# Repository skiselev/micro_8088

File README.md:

# Micro 8088
IBM XT Compatible Processor Board based on Faraday FE2010/FE2010A chipset

## Introduction
Micro 8088 is an easy to build IBM PC/XT compatible processor board. It uses a fairly common Faraday FE2010/FE2010A chipset, that implements most of IBM PC/XT LSIs (Intel 8xxx ICs) and glue logic. Micro 8088 uses SRAM ICs to implement the system RAM, and a Flash ROM IC to store the BIOS, further reducing the number of components, and simplifying the build process.

## Specifications
* Processor: Intel 8088 or compatible, NEC V20
  * Supports IBM PC/XT standard 4.77 MHz CPU frequency and, when using FE2010A chipset, 7.16 MHz and 9.54 MHz CPU frequencies
* Coprocessor: Intel 8087
* [Faraday FE2010/FE2010A](Documentation/Faraday-XT_Controller-FE2010A.md) chipset, implementing the following components:
  * One 8237 direct memory access controller (DMAC)
  * One 8259 programmable interrupt controller (PIC)
  * One 8254 programmable interval timer (PIT)
  * One 8255 programmable peripheral interface (PPI)
  * Clock generation, and glue logic
* RAM: 512 KiB or 640 KiB base memory; Up to 192 KiB UMBs. Implemented using SRAM
* ROM: 64 KiB. Implemented using 128 KiB Flash ROM
* 8-bit ISA interface
* PS/2 compatible keyboard connector; built in AT2XT converter

## Hardware Documentation

### Schematic and PCB Layout

[Schematic - Version 1.1](KiCad/8088-FE2010A-SBC-Schematic-1.1.pdf)

[PCB Layout - Version 1.1](KiCad/8088-FE2010A-SBC-Board-1.1.pdf)

[PCB Layout - Version 1.2](KiCad/8088-FE2010A-SBC-Board-1.2.pdf)

[PCB Layout - Version 1.3](KiCad/8088-FE2010A-SBC-Board-1.3.pdf)

### Building Insturctions

Please refer to [Building Instructions](Building_Instructions.md) page for detailed instructions.

### Faraday FE2010/FE2010A Information

Please refer to [Faraday FE2010A documentation](Documentation/Faraday-XT_Controller-FE2010A.md) and [Faraday FE2010 datasheet](Documentation/Faraday-XT_Controller-FE2010.pdf) for detailed information about Faraday FE2010/FE2010A chipsets.

*Note: CPU clock frequency switching (turbo mode) is only implemented in Faraday FE2010A chipset (not in FE2010).*

### Jumpers, Connectors, and Switches

#### P1 - PS/2 Keyboard
Pin | Description
--- | -----------
1   | Keyboard data
2   |	Unused
3   |	GND
4   |	+5V
5   |	Keyboard clock
6   |	Unused

#### P2 - Speaker
Pin | Description
--- | -----------
1   | Speaker output
2   | Internal Speaker input*
3   | Unused
4   |	+5V

*Note: To enable internal speaker connect a jumper across pins 1-2*

#### P3 - Reset Switch
Pin | Description
--- | -----------
1   | Reset input
2   | Ground

#### JP1 - Select Flash ROM area mapped to 0xF0000-0xFFFFF
Position | Description
-------- | -----------
*open (default)* | Map lower 64 KiB of the Flash ROM to 0xF0000-0xFFFFF
closed   | Map upper 64 KiB of the Flash ROM to 0xF0000-0xFFFFF

#### JP2 - Select X1 Crystal Frequency
Position | Description
-------- | -----------
open     | Use 14.31818 MHz crystal
*closed (default)* | Use 28.63636 MHz crystal

*Note: 14.31818 MHz crystal supports 4.77 MHz and 7.16 MHz CPU clock frequencies; 28.63636 MHz crystal additionally supports 9.55 MHz CPU clock frequency*

#### JP3 - RAM Chip Select Source
Position | Description
-------- | -----------
*open (default)* | Use SPLD (U16)
closed   | Use FE2010A (U3)

*Note: FE2010A only generates RAM chip select for the base RAM (lower 640 KiB). It does not generate RAM chip select for UMBs, and therefore SPLD (U16) is required to implement UMBs*

#### JP4 - Flash ROM Chip Select Source
Position | Description
-------- | -----------
*open (default)* | Use SPLD (U16)
closed   | Use FE2010A (U3)

*Note: FE2010A does not generate chip select for memory write cycles, therefore it does not support in-system BIOS upgrades*

#### SW1 - Reset Switch
Press SW1 to reset the system

#### SW2 - System Configuration
Position	| Description
-------- | -----------
SW2.1 = OFF, SW2.2 = OFF | MDA or Hercules
SW2.1 = ON, SW2.2 = OFF  | CGA, 80x25
SW2.1 = OFF, SW2.2 = ON  | CGA, 40x25
SW2.1 = ON, SW2.2 = ON   | None, EGA, or VGA
SW2.3 = OFF | Disable keyboard 0xE0 scan code pass through
SW2.3 = ON | Enable keyboard 0xE0 scan code pass through

#### SW3 - UMB Configuration
Position	| Description
-------- | -----------
SW3.1 = ON | Map 0xC0000-0xC7FFF to RAM 
SW3.2 = ON | Map 0xC8000-0xCFFFF to RAM 
SW3.3 = ON | Map 0xD0000-0xD7FFF to RAM 
SW3.4 = ON | Map 0xD8000-0xDFFFF to RAM 
SW3.5 = ON | Map 0xE0000-0xEFFFF to RAM

*Note: SPLD (U16) is required to implement UMBs. This switch is not used in systems without SPLD*

### Bill of Materials - Versions 1.1, 1.2, and 1.3

[Micro 8088 project on Mouser.com](https://www.mouser.com/ProjectManager/ProjectDetail.aspx?AccessID=57e2f0df1d) - View and order all components except of the Faraday FE2010A chipset, and the PCB.
[Micro 8088 project on OSH Park](https://oshpark.com/shared_projects/xbWzfre6) - View and order the PCB.

Component type    	| Reference | Description                       | Quantity | Possible sources and notes 
------------------ | --------- | --------------------------------- | -------- | --------------------------
PCB                |           | Micro 8080 PCB - Version 1.1, 1.2, or 1.3 | 1        | Refer to the [RetroBrew Computers Board Inventory](https://retrobrewcomputers.org/doku.php?id=boardinventory#xi_8088_project_sergey_kiselev) page for ordering information, or order from a PCB manufacturer of your choice using provided Gerber or KiCad files
Integrated Circuit | U1        | Intel 8088, 80C88, or NEC V20 CPU | 1        | eBay, Mouser (expensive) - [968-CP80C88-2Z](https://www.mouser.com/ProductDetail/968-CP80C88-2Z)
Integrated Circuit | U2        | Intel 8087 FPU                    | 1        | Optional, eBay
Integrated Circuit | U3        | Faraday FE2010A                   | 1        | eBay, can be replaced with [Proton PT8010AF](https://github.com/skiselev/micro_8088/blob/master/Documentation/Proton-XT_Controller-PT8010AF.md)
Integrated Circuit | U4        | SST39SF010A Flash ROM, DIP-32 package | 1    | Mouser [804-39SF010A7CPHE](https://www.mouser.com/ProductDetail/804-39SF010A7CPHE)
Integrated Circuit | U5, U6    | AS6C4008 SRAM, DIP-32 package     | 2        | Mouser [913-AS6C4008-55PCN](https://www.mouser.com/ProductDetail/913-AS6C4008-55PCN)
Integrated Circuit | U7 - U9   | 74F573 Octal D-Type Latch         | 3        | Mouser [595-SN74F573N](https://www.mouser.com/ProductDetail/595-SN74F573N)
Integrated Circuit | U10, U11  | 74F245 Octal Bus Transceiver      | 2        | Mouser [595-SN74F245N](https://www.mouser.com/ProductDetail/595-SN74F245N)
Integrated Circuit | U12, U13  | 74F244 Octal Buffer               | 2        | Mouser [595-SN74F244N](https://www.mouser.com/ProductDetail/595-SN74F244N)
Integrated Circuit | U14       | 74F00 Quad 2-Input NAND Gate      | 1        | Mouser [595-SN74F00](https://www.mouser.com/ProductDetail/595-SN74F00N). **Important note: install either U14 or U16, not both together**
Integrated Circuit | U15       | PIC12F629 Microcontroller         | 1        | Mouser [PIC12F629-I-P](https://www.mouser.com/ProductDetail/579-PIC12F629IP)
Integrated Circuit | U16       | ATF16V8B SPLD                     | 1        | Mouser [556-AF16V8B15PU](https://www.mouser.com/ProductDetail/556-AF16V8B15PU). **Important note: install either U14 or U16, not both together**
IC Socket          | U1, U2    | DIP-40, 600 mil socket            | 2        | Mouser [649-DILB40P223TLF](https://www.mouser.com/ProductDetail/649-DILB40P223TLF)
IC Socket          | U3        | PLCC-84 through hole socket       | 1        | Mouser [517-8484-11B1-RK-TP](https://www.mouser.com/ProductDetail/517-8484-11B1-RK-TP)
IC Socket          | U4-U6     | DIP-32, 600 mil socket            | 3        | Mouser [649-DILB32P223TLF](https://www.mouser.com/ProductDetail/649-DILB32P223TLF)
IC Socket          | U7-U13, U16 | DIP-20, 300 mil socket          | 8        | Mouser [649-DILB20P-223TLF](https://www.mouser.com/ProductDetail/649-DILB20P-223TLF)
IC Socket          | U14       | DIP-14, 300 mil socket            | 1        | Mouser [649-DILB14P-223TLF](https://www.mouser.com/ProductDetail/649-DILB14P-223TLF)
IC Socket          | U15       | DIP-8, 300 mil socket             | 1        | Mouser [649-DILB8P223TLF](https://www.mouser.com/ProductDetail/649-DILB8P223TLF)
Diode              | D1        | 1N4148                            | 1        | Mouser [512-1N4148](https://www.mouser.com/ProductDetail/512-1N4148)
LED                | D2        | 3 mm, green LED indicator         | 1        | Mouser [LTL-4231NHBP](https://www.mouser.com/ProductDetail/859-LTL-4231NHBP)
Transistor         | Q1        | PN2222A, 2.54mm lead spacing      | 1        | Mouser [512-PN2222ATA](https://www.mouser.com/ProductDetail/512-PN2222ATA)
Crystal            | X1        | 28.63636 MHz, 18 pF, HC-49/S      | 1        | Mouser [717-9B-28.63636MAAJB](https://www.mouser.com/ProductDetail/717-9B-28.63636MAAJB)
Speaker            | SP1       | 12 mm speaker                     | 1        | Mouser [665-AT-1224TWTR](https://www.mouser.com/ProductDetail/665-AT-1224TWTR)
Tactile Button     | SW1       | 6 mm tactile button, right angle  | 1        | Mouser [653-B3F-3152](https://www.mouser.com/ProductDetail/653-B3F-3152)
DIP Switch         | SW2       | 3 positions                       | 1        | Mouser [774-2063](https://www.mouser.com/ProductDetail/774-2063)
DIP Switch         | SW3       | 5 positions                       | 1        | Mouser [774-2065](https://www.mouser.com/ProductDetail/774-2065)
Connector          | P1        | 6 pin Mini DIN, purple            | 1        | Mouser [806-KMDGX-6S-BS](https://www.mouser.com/ProductDetail/806-KMDGX-6S-BS)
Pin Header         | P2, JP3-JP4 | 4 pin header, 2.54 mm pitch     | 2        | Mouser [649-68002-104HLF](https://www.mouser.com/ProductDetail/649-68002-104HLF)
Pin Header         | P3, JP1-JP2 | 2 pin header, 2.54 mm pitch     | 3        | Mouser [649-68002-102HLF](https://www.mouser.com/ProductDetail/649-68002-102HLF)
Capacitor          | C1 - C17  | 0.1 uF, MLCC, 5 mm lead spacing   | 17       | Mouser [810-FG28X7R1H104KNT6](https://www.mouser.com/ProductDetail/810-FG28X7R1H104KNT6)
Capacitor          | C18 - C20 | 10 uF, MLCC, 5 mm lead spacing    | 3        | Mouser [810-FG28X5R1E106MR06](https://www.mouser.com/ProductDetail/810-FG28X5R1E106MR06)
Trimmer Capacitor  | C21       | 6.5-30 pF, 5 mm lead spacing      | 1        | Mouser [659-GKG30015](https://www.mouser.com/ProductDetail/659-GKG30015). Note: Trimmer capacitor is used to fine-tune 14.31818 MHz OSC frequency, and it might be needed when using CGA graphics with composite display. If not using CGA with composite display, a 22pF or so ceramic capacitor can be used instead, such as Mouser [810-FG28C0G1H220JNT6](https://www.mouser.com/ProductDetail/810-FG28C0G1H220JNT6)
Capacitor          | C22       | 47 pF, MLCC, 5 mm lead spacing    | 1        | Mouser [810-FG28C0G1H470JNT6](https://www.mouser.com/ProductDetail/810-FG28C0G1H470JNT6)
Capacitor          | C23       | 0.01 uF, MLCC, 5 mm lead spacing  | 1        | Mouser [810-FG28X7R1H103KNT6](https://www.mouser.com/ProductDetail/810-FG28X7R1H103KNT6)
Resistor Array     | RR1       | 4.7 k, bussed, 10 pin SIP         | 1        | Mouser [652-4610X-1LF-4.7K](https://www.mouser.com/ProductDetail/652-4610X-1LF-4.7K)
Resistor Array     | RR2       | 10 k, bussed, 10 pin SIP          | 1        | Mouser [652-4610X-1LF-10K](https://www.mouser.com/ProductDetail/652-4610X-1LF-10K)
Resistor Array     | RR3, RR4  | 4.7 k, bussed, 6 pin SIP          | 2        | Mouser [652-4606X-1LF-4.7K](https://www.mouser.com/ProductDetail/652-4606X-1LF-4.7K)
Resistor Array     | RR5       | 10 k, bussed, 6 pin SIP           | 1        | Mouser [652-4606X-1LF-10K](https://www.mouser.com/ProductDetail/652-4606X-1LF-10K)
Resistor           | R1        | 33 ohm, through hole              | 1        | Mouser [603-MFR-25FBF52-33R](https://www.mouser.com/ProductDetail/603-MFR-25FBF52-33R)
Resistor           | R2, R3    | 47 ohm, through hole              | 2        | Mouser [603-MFR-25FBF52-47R](https://www.mouser.com/ProductDetail/603-MFR-25FBF52-47R)
Resistor           | R4, R5    | 470 ohm, through hole             | 2        | Mouser [603-MFR-25FBF52-470R](https://www.mouser.com/ProductDetail/603-MFR-25FBF52-470R)
Resistor           | R6        | 1 kohm, through hole              | 1        | Mouser [603-MFR-25FBF52-1K](https://www.mouser.com/ProductDetail/603-MFR-25FBF52-1K)
Resistor           | R7        | 10 kohm, through hole             | 1        | Mouser [603-MFR-25FBF52-10K](https://www.mouser.com/ProductDetail/603-MFR-25FBF52-10K)
Resistor           | R8        | 1 Mohm, through hole              | 1        | Mouser [603-MFR-25FBF52-1M](https://www.mouser.com/ProductDetail/603-MFR-25FBF52-1M)
Fuse               | F1        | 1.1A polyfuse, 5.08 mm lead pitch | 1        | Mouser [650-RUSBF110-2](https://www.mouser.com/ProductDetail/650-RUSBF110-2)
ISA Bracket        |           | Keystone Electronics 9202         | 1        | Mouser [534-9202](https://www.mouser.com/ProductDetail/534-9202)
Screw              |           | 4-40 x 1/4" Screw                 | 2        | Mouser [534-9900](https://www.mouser.com/ProductDetail/534-9900)

## Firmware Documentation

### System BIOS

Micro 8088 uses a modified version of [Xi 8088](http://www.malinov.com/Home/sergeys-projects/xi-8088) BIOS. The BIOS binary images are provided in [BIOS](BIOS) directory. The BIOS source code is available in [8088_bios GitHub repository](https://github.com/skiselev/8088_bios)

#### Turbo Mode Switching

The BIOS keyboard handler uses the following key combinations to switch the CPU clock frequency:
* **Ctrl-Alt-Keypad -** - Normal 4.77 MHz CPU clock frequency
* **Ctrl-Alt-Keypad \*** - Turbo 7.16 MHz CPU clock frequency
* **Ctrl-Alt-Keypad +** - Turbo 9.55 MHz CPU clock frequency (works only on systems with 28.63636 MHz X1 crystal)

Note that the BIOS does not, and possibly can not check if the installed CPU and the FPU are actually capable of running at higher clock frequencies. Turning on the turbo mode in a system with 5 MHz CPU can make it unstable.

### AT2XT Firmware

Micro 8088 integrates an AT2XT keyboard converter, implemented using PIC12F629 (U15). The firmware for this microcontroller is availabe from the [minuszerodegrees.net](http://minuszerodegrees.net/at2xtkb/XTATKEY_094.zip) and the [Vintage Computer Federation AT2XT page](https://forum.vcfed.org/index.php?threads/at2xt-keyboard-converter.26861/page-4#post-1242916). The HEX file with the firmware can be extracted from XTATKEY_094.zip.

### SPLD Fuse Maps

An optional ATF16V8/GAL16V8 SPLD (U16) allows using spare SRAM space for UMBs, and implements Flash ROM write access. The fuse maps for the SPLD are provided in [SPLD](SPLD) directory of this repository. The [SPLD/micro_8088_prod.jed](SPLD/micro_8088_prod.jed) fuse map should be used for production applications.

## Changes
* Version 1.3
  * Update silkscreen:
    * SW2.3 - fix the description for the *ON* position
    * Add a warning about installing either U14 or U16, but not both
    * Update board version to 1.3
* Version 1.2
  * Update silkscreen:
    * JP2 - change the default to *Closed*
    * Bracket - move rectangles to the back side, add circles around mounting holes on the front side
    * Remove the line around ISA connector
    * Use KiCad OSHW logo
    * Update copyright years to 2017-2018
    * Update board version to 1.2
* Version 1.1
  * Recommend using 74F-series, and update the schematic and the silkscreen accordingly. 74F-series ICs are faster and slightly cheaper than 74ALS-series
  * Add 74F573 latch for latching A8-A11 signals. This fixes the DMA issue
  * Use 74F244 to buffer OSC and CLK signals
  * Use AS6C4008 for the second SRAM (U6) instead of AS6C1004. This resolves the AS6C1004 TTL compatibility issue
  * Use 74F00 for generating chip select signal for the second SRAM (U6), and for inverting the speaker signal
  * Add an optional SPLD (U16) to implement UMBs
  * Use 128 KiB Flash ROM instead of 32 KiB EEPROM. It is cheaper, and has twice more storage space
  * Use buffered /MEMR and /MEMW signals for SRAM and BIOS ROM
  * PCB dimensions changed from 5" x 4.3" to 6" x 4"
* Version 1.0
  * Initial version

## Known Issues
* Version 1.2
  * SW2.3 description on the back silkscreen incorrectly references SW1.3 for the *ON* position
* Version 1.1
  * JP2 description on the back silkscreen suggests that the default JP2 position is *Open*. Since the recommended chipset is FE2010A and the recommended crystal frequency is 28.63636 MHz, the default JP2 position should be *Closed*
  * Update the silkscreen near ISA bracket mounting holes: The rectangles should be moved to the back silkscreen, and screw head sized circles should be shown on the front skilscreen
* Version 1.0
  * AS6C1008 (U6) does not have TTL compatible inputs causing instability with 640 KiB memory configruation
    * Workaround: use CMOS transceiver U11, e.g. 74AHCT245
  * DMA doesn't work properly.
    * This is due to A8-A11 address lines not being latched.
    * Workaround: add a 74F573 latch, and connect AA8-AA11 and A8-AA11 through it

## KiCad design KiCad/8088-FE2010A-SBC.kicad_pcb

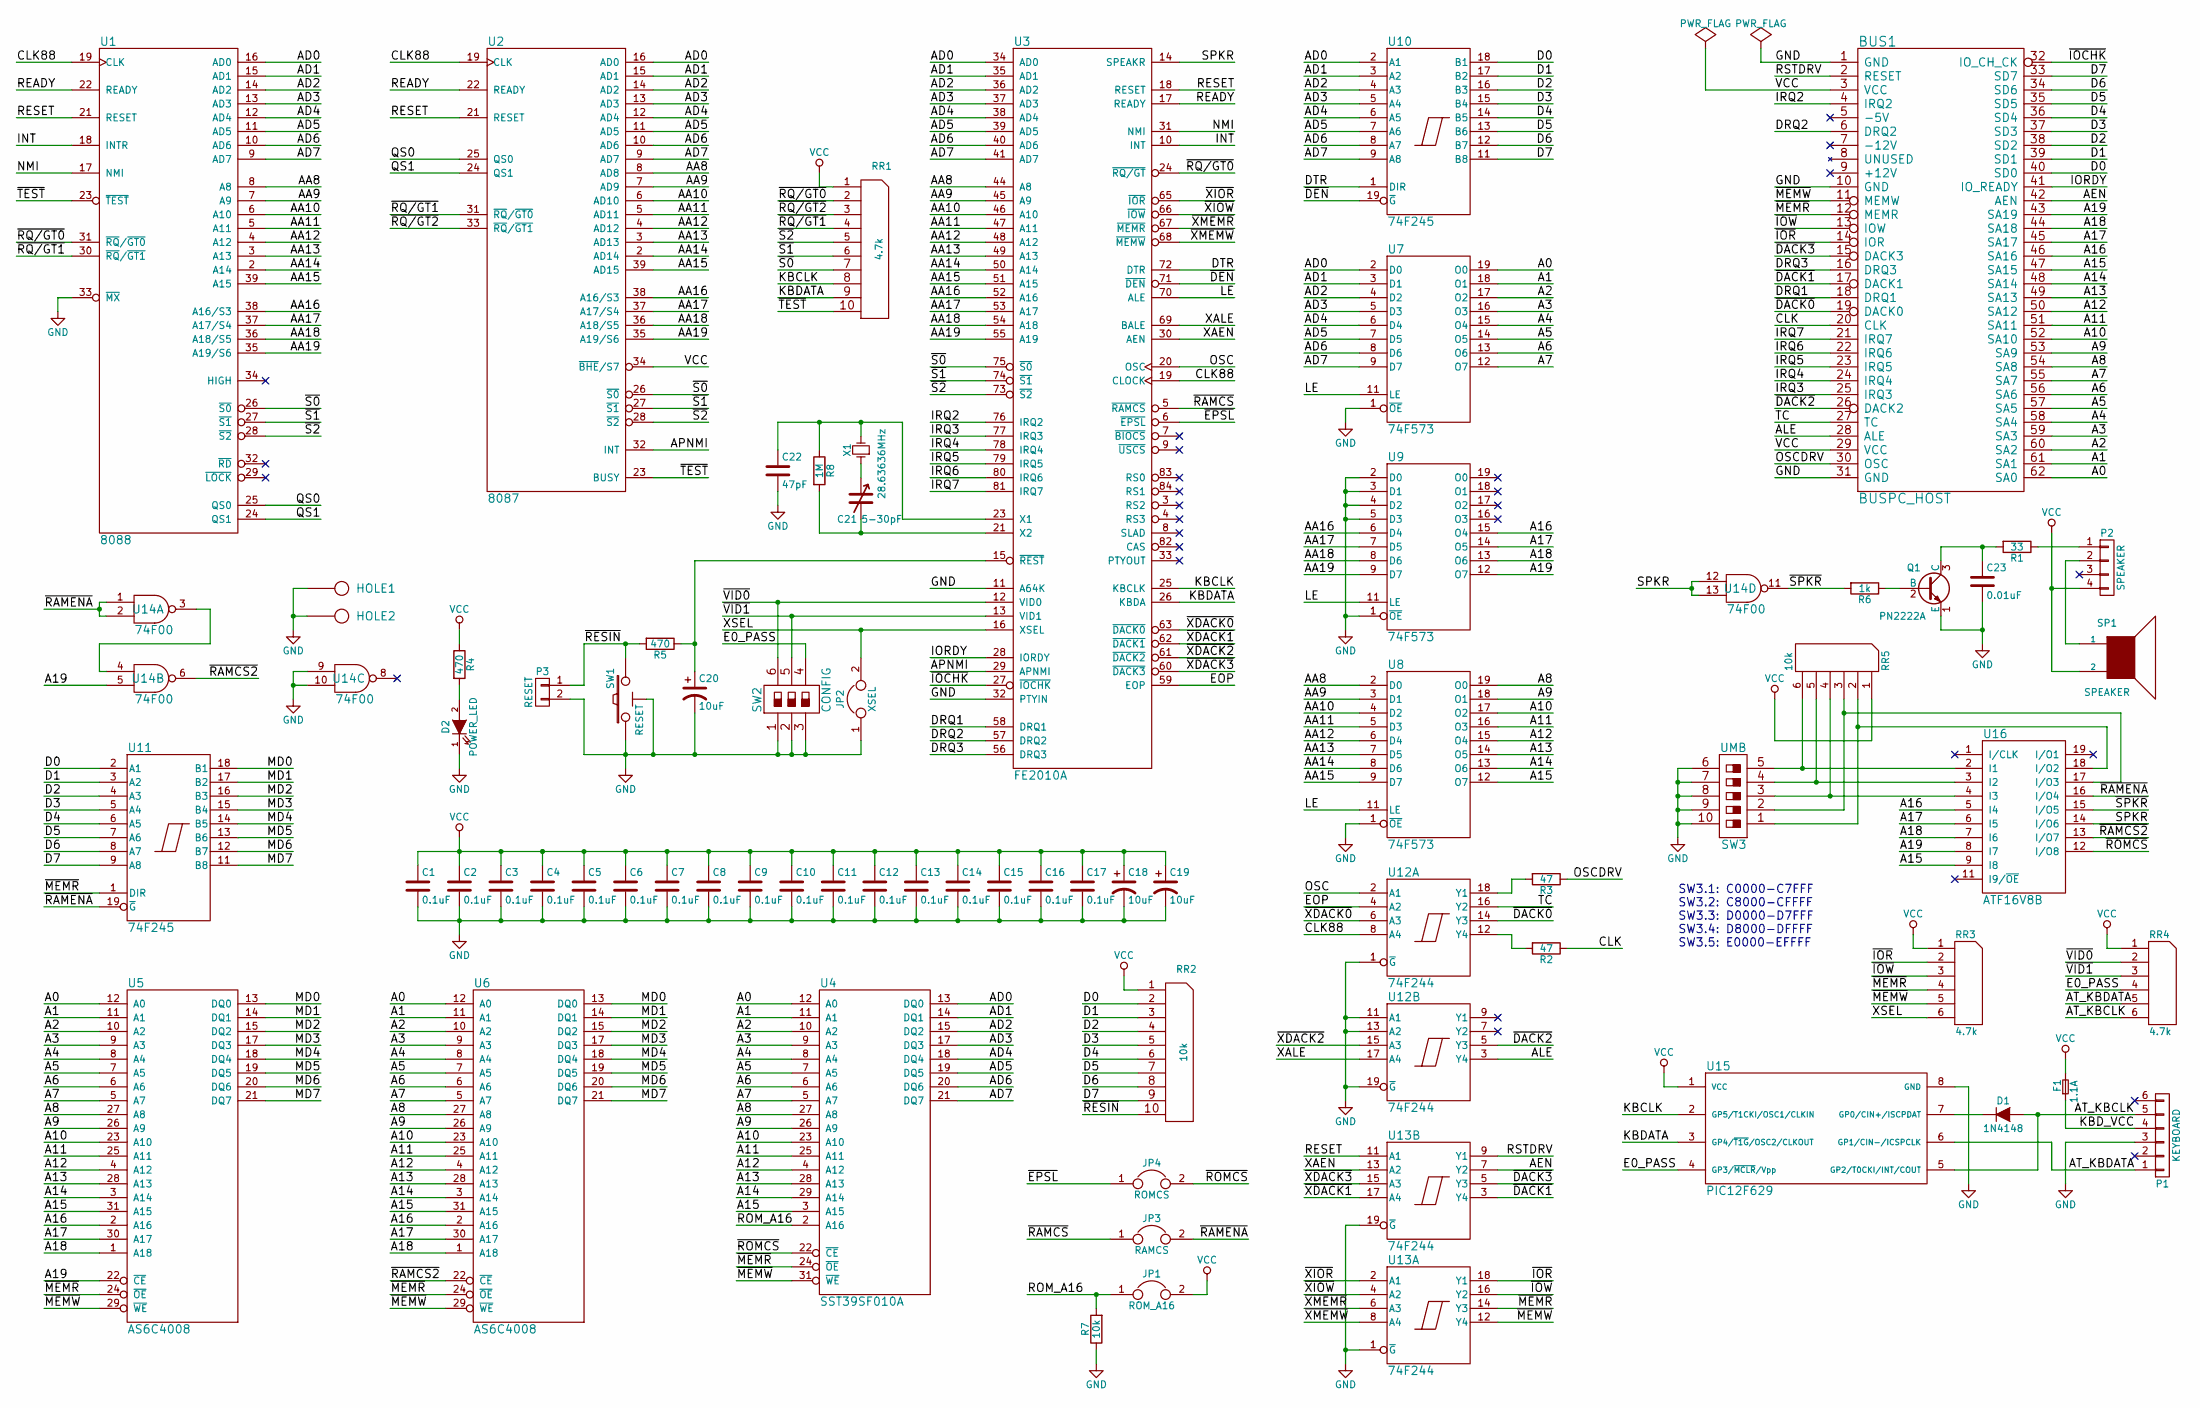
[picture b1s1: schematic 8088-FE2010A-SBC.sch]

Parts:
BUS1: BUSPC_HOST; Conn_Edge_PCB_ISA8
C1, C2, C3, C4, C5, C6, C7, C8, C9, C10, C11, C12, C13, C14, C15, C16, C17: 0.1uF; Cap_Cer_508
C18, C19, C20: 10uF; Cap_Tant_508
C21: 5-30pF; C_Trim_Murata
C22: 47pF; Cap_Cer_508
C23: 0.01uF; Cap_Cer_508
D1: 1N4148; Diode_762
D2: POWER_LED; LED_3mm
F1: 1.1A; Cap_Cer_508
HOLE1, HOLE2: HOLE; Hole_3mm
JP1: ROM_A16; Conn_Pin_Header_2x1_2.54mm_NoKey
JP2: XSEL; Conn_Pin_Header_2x1_2.54mm_NoKey
JP3: RAMCS; Conn_Pin_Header_2x1_2.54mm_NoKey
JP4: ROMCS; Conn_Pin_Header_2x1_2.54mm_NoKey
P1: KEYBOARD; Conn_Mini_DIN_6pin
P2: SPEAKER; Conn_Pin_Header_4x1_2.54mm
P3: RESET; Conn_Pin_Header_2x1_2.54mm
Q1: PN2222A; Transistor_TO92_EBC_254
R1: 33; Res_762
R2, R3: 47; Res_762
R4, R5: 470; Res_762
R6: 1k; Res_762
R7: 10k; Res_762
R8: 1M; Res_762
RR1: 4.7k; Conn_SIL10
RR2: 10k; Conn_SIL10
RR3, RR4: 4.7k; Conn_SIL6
RR5: 10k; Conn_SIL6
SP1: SPEAKER; Speaker_12mm
SW1: RESET; Switch_Tactile_6mm_Right
SW2: CONFIG; Switch_DIP_3_Positions
SW3: UMB; Switch_DIP_5_Positions
U1: 8088; IC_DIP40_600
U2: 8087; IC_DIP40_600
U3: FE2010A; IC_PLCC84_TH
U4: SST39SF010A; IC_DIP32_600
U5, U6: AS6C4008; IC_DIP32_600
U7, U8, U9: 74F573; IC_DIP20_300
U10, U11: 74F245; IC_DIP20_300
U12, U13: 74F244; IC_DIP20_300
U14: 74F00; IC_DIP14_300
U15: PIC12F629; IC_DIP8_300
U16: ATF16V8B; IC_DIP20_300
X1: 28.63636MHz; Crystal_HC-49U_Vert

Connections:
/A0: BUS1.62 (SA0), U4.12 (A0), U5.12 (A0), U6.12 (A0), U7.19 (O0)
/A1: BUS1.61 (SA1), U4.11 (A1), U5.11 (A1), U6.11 (A1), U7.18 (O1)
/A2: BUS1.60 (SA2), U4.10 (A2), U5.10 (A2), U6.10 (A2), U7.17 (O2)
/A3: BUS1.59 (SA3), U4.9 (A3), U5.9 (A3), U6.9 (A3), U7.16 (O3)
/A4: BUS1.58 (SA4), U4.8 (A4), U5.8 (A4), U6.8 (A4), U7.15 (O4)
/A5: BUS1.57 (SA5), U4.7 (A5), U5.7 (A5), U6.7 (A5), U7.14 (O5)
/A6: BUS1.56 (SA6), U4.6 (A6), U5.6 (A6), U6.6 (A6), U7.13 (O6)
/A7: BUS1.55 (SA7), U4.5 (A7), U5.5 (A7), U6.5 (A7), U7.12 (O7)
/A8: BUS1.54 (SA8), U4.27 (A8), U5.27 (A8), U6.27 (A8), U8.19 (O0)
/A9: BUS1.53 (SA9), U4.26 (A9), U5.26 (A9), U6.26 (A9), U8.18 (O1)
/A10: BUS1.52 (SA10), U4.23 (A10), U5.23 (A10), U6.23 (A10), U8.17 (O2)
/A11: BUS1.51 (SA11), U4.25 (A11), U5.25 (A11), U6.25 (A11), U8.16 (O3)
/A12: BUS1.50 (SA12), U4.4 (A12), U5.4 (A12), U6.4 (A12), U8.15 (O4)
/A13: BUS1.49 (SA13), U4.28 (A13), U5.28 (A13), U6.28 (A13), U8.14 (O5)
/A14: BUS1.48 (SA14), U4.29 (A14), U5.3 (A14), U6.3 (A14), U8.13 (O6)
/A15: BUS1.47 (SA15), U4.3 (A15), U5.31 (A15), U6.31 (A15), U8.12 (O7), U16.9 (I8)
/A16: BUS1.46 (SA16), U5.2 (A16), U6.2 (A16), U9.15 (O4), U16.5 (I4)
/A17: BUS1.45 (SA17), U5.30 (A17), U6.30 (A17), U9.14 (O5), U16.6 (I5)
/A18: BUS1.44 (SA18), U5.1 (A18), U6.1 (A18), U9.13 (O6), U16.7 (I6)
/A19: BUS1.43 (SA19), U5.22 (~CE), U9.12 (O7), U14.5, U16.8 (I7)
/AA8: U1.8 (A8), U2.8 (AD8), U3.44 (A8), U8.2 (D0)
/AA9: U1.7 (A9), U2.7 (AD9), U3.45 (A9), U8.3 (D1)
/AA10: U1.6 (A10), U2.6 (AD10), U3.46 (A10), U8.4 (D2)
/AA11: U1.5 (A11), U2.5 (AD11), U3.47 (A11), U8.5 (D3)
/AA12: U1.4 (A12), U2.4 (AD12), U3.48 (A12), U8.6 (D4)
/AA13: U1.3 (A13), U2.3 (AD13), U3.49 (A13), U8.7 (D5)
/AA14: U1.2 (A14), U2.2 (AD14), U3.50 (A14), U8.8 (D6)
/AA15: U1.39 (A15), U2.39 (AD15), U3.51 (A15), U8.9 (D7)
/AA16: U1.38 (A16/S3), U2.38 (A16/S3), U3.52 (A16), U9.6 (D4)
/AA17: U1.37 (A17/S4), U2.37 (A17/S4), U3.53 (A17), U9.7 (D5)
/AA18: U1.36 (A18/S5), U2.36 (A18/S5), U3.54 (A18), U9.8 (D6)
/AA19: U1.35 (A19/S6), U2.35 (A19/S6), U3.55 (A19), U9.9 (D7)
/AD0: U1.16 (AD0), U2.16 (AD0), U3.34 (AD0), U4.13 (DQ0), U7.2 (D0), U10.2 (A1)
/AD1: U1.15 (AD1), U2.15 (AD1), U3.35 (AD1), U4.14 (DQ1), U7.3 (D1), U10.3 (A2)
/AD2: U1.14 (AD2), U2.14 (AD2), U3.36 (AD2), U4.15 (DQ2), U7.4 (D2), U10.4 (A3)
/AD3: U1.13 (AD3), U2.13 (AD3), U3.37 (AD3), U4.17 (DQ3), U7.5 (D3), U10.5 (A4)
/AD4: U1.12 (AD4), U2.12 (AD4), U3.38 (AD4), U4.18 (DQ4), U7.6 (D4), U10.6 (A5)
/AD5: U1.11 (AD5), U2.11 (AD5), U3.39 (AD5), U4.19 (DQ5), U7.7 (D5), U10.7 (A6)
/AD6: U1.10 (AD6), U2.10 (AD6), U3.40 (AD6), U4.20 (DQ6), U7.8 (D6), U10.8 (A7)
/AD7: U1.9 (AD7), U2.9 (AD7), U3.41 (AD7), U4.21 (DQ7), U7.9 (D7), U10.9 (A8)
/AEN: BUS1.42 (AEN), U13.7 (Y2)
/ALE: BUS1.28 (ALE), U12.3 (Y4)
/APNMI: U2.32 (INT), U3.29 (APNMI)
/AT_KBCLK: D1.2 (A), P1.5, RR4.6, U15.5 (GP2/T0CKI/INT/COUT)
/AT_KBDATA: P1.1, RR4.5, U15.6 (GP1/CIN-/ICSPCLK)
/CLK: BUS1.20 (CLK), R2.1
/CLK88: U1.19 (CLK), U2.19 (CLK), U3.19 (CLOCK), U12.8 (A4)
/D0: BUS1.40 (SD0), RR2.2, U10.18 (B1), U11.2 (A1)
/D1: BUS1.39 (SD1), RR2.3, U10.17 (B2), U11.3 (A2)
/D2: BUS1.38 (SD2), RR2.4, U10.16 (B3), U11.4 (A3)
/D3: BUS1.37 (SD3), RR2.5, U10.15 (B4), U11.5 (A4)
/D4: BUS1.36 (SD4), RR2.6, U10.14 (B5), U11.6 (A5)
/D5: BUS1.35 (SD5), RR2.7, U10.13 (B6), U11.7 (A6)
/D6: BUS1.34 (SD6), RR2.8, U10.12 (B7), U11.8 (A7)
/D7: BUS1.33 (SD7), RR2.9, U10.11 (B8), U11.9 (A8)
/DRQ1: BUS1.18 (DRQ1), U3.58 (DRQ1)
/DRQ2: BUS1.6 (DRQ2), U3.57 (DRQ2)
/DRQ3: BUS1.16 (DRQ3), U3.56 (DRQ3)
/DTR: U3.72 (DTR), U10.1 (DIR)
/E0_PASS: RR4.4, SW2.4, U15.4 (GP3/~MCLR~/Vpp)
/EOP: U3.59 (EOP), U12.4 (A2)
/INT: U1.18 (INTR), U3.10 (INT)
/IORDY: BUS1.41 (IO_READY), U3.28 (IORDY)
/IRQ2: BUS1.4 (IRQ2), U3.76 (IRQ2)
/IRQ3: BUS1.25 (IRQ3), U3.77 (IRQ3)
/IRQ4: BUS1.24 (IRQ4), U3.78 (IRQ4)
/IRQ5: BUS1.23 (IRQ5), U3.79 (IRQ5)
/IRQ6: BUS1.22 (IRQ6), U3.80 (IRQ6)
/IRQ7: BUS1.21 (IRQ7), U3.81 (IRQ7)
/KBCLK: RR1.8, U3.25 (KBCLK), U15.2 (GP5/T1CKI/OSC1/CLKIN)
/KBDATA: RR1.9, U3.26 (KBDA), U15.3 (GP4/~T1G~/OSC2/CLKOUT)
/KBD_VCC: F1.1, P1.4
/LE: U3.70 (ALE), U7.11 (LE), U8.11 (LE), U9.11 (LE)
/MD0: U5.13 (DQ0), U6.13 (DQ0), U11.18 (B1)
/MD1: U5.14 (DQ1), U6.14 (DQ1), U11.17 (B2)
/MD2: U5.15 (DQ2), U6.15 (DQ2), U11.16 (B3)
/MD3: U5.17 (DQ3), U6.17 (DQ3), U11.15 (B4)
/MD4: U5.18 (DQ4), U6.18 (DQ4), U11.14 (B5)
/MD5: U5.19 (DQ5), U6.19 (DQ5), U11.13 (B6)
/MD6: U5.20 (DQ6), U6.20 (DQ6), U11.12 (B7)
/MD7: U5.21 (DQ7), U6.21 (DQ7), U11.11 (B8)
/NMI: U1.17 (NMI), U3.31 (NMI)
/OSC: U3.20 (OSC), U12.2 (A1)
/OSCDRV: BUS1.30 (OSC), R3.1
/QS0: U1.25 (QS0), U2.25 (QS0)
/QS1: U1.24 (QS1), U2.24 (QS1)
/READY: U1.22 (READY), U2.22 (READY), U3.17 (READY)
/RESET: U1.21 (RESET), U2.21 (RESET), U3.18 (RESET), U13.11 (A1)
/ROM_A16: JP1.1, R7.2, U4.2 (A16)
/RSTDRV: BUS1.2 (RESET), U13.9 (Y1)
/SPKR: U3.14 (SPEAKR), U14.12, U14.13, U16.14 (I/O6)
/TC: BUS1.27 (TC), U12.16 (Y2)
/XAEN: U3.30 (AEN), U13.13 (A2)
/XALE: U3.69 (BALE), U12.17 (A4)
/XSEL: JP2.2, RR3.6, U3.16 (XSEL)
/~DACK0: BUS1.19 (DACK0), U12.14 (Y3)
/~DACK1: BUS1.17 (DACK1), U13.3 (Y4)
/~DACK2: BUS1.26 (DACK2), U12.5 (Y3)
/~DACK3: BUS1.15 (DACK3), U13.5 (Y3)
/~DEN: U3.71 (~DEN), U10.19 (~G)
/~EPSL: JP4.1, U3.6 (~EPSL)
/~IOCHK: BUS1.32 (IO_CH_CK), U3.27 (~IOCHK)
/~IOR: BUS1.14 (IOR), RR3.2, U13.18 (Y1)
/~IOW: BUS1.13 (IOW), RR3.3, U13.16 (Y2)
/~MEMR: BUS1.12 (MEMR), RR3.4, U4.24 (~OE), U5.24 (~OE), U6.24 (~OE), U11.1 (DIR), U13.14 (Y3)
/~MEMW: BUS1.11 (MEMW), RR3.5, U4.31 (~WE), U5.29 (~WE), U6.29 (~WE), U13.12 (Y4)
/~RAMCS: JP3.1, U3.5 (~RAMCS)
/~RAMCS2: U6.22 (~CE), U14.6, U16.13 (I/O7)
/~RAMENA: JP3.2, U11.19 (~G), U14.1, U14.2, U16.16 (I/O4)
/~RESIN: P3.1, R5.2, RR2.10, SW1.2
/~ROMCS: JP4.2, U4.22 (~CE), U16.12 (I/O8)
/~RQ/GT0: RR1.2, U1.31 (~RQ~/~GT0~), U3.24 (~RQ/GT)
/~RQ/GT1: RR1.4, U1.30 (~RQ~/~GT1~), U2.31 (~RQ~/~GT0~)
/~RQ/GT2: RR1.3, U2.33 (~RQ~/~GT1~)
/~S0: RR1.7, U1.26 (~S0), U2.26 (~S0), U3.75 (~S0)
/~S1: RR1.6, U1.27 (~S1), U2.27 (~S1), U3.74 (~S1)
/~S2: RR1.5, U1.28 (~S2), U2.28 (~S2), U3.73 (~S2)
/~SPKR: R6.2, U14.11, U16.15 (I/O5)
/~TEST: RR1.10, U1.23 (~TEST), U2.23 (BUSY)
/~VID0: RR4.2, SW2.6, U3.12 (VID0)
/~VID1: RR4.3, SW2.5, U3.13 (VID1)
/~XDACK0: U3.63 (~DACK0), U12.6 (A3)
/~XDACK1: U3.62 (~DACK1), U13.17 (A4)
/~XDACK2: U3.61 (~DACK2), U12.15 (A3)
/~XDACK3: U3.60 (~DACK3), U13.15 (A3)
/~XIOR: U3.65 (~IOR), U13.2 (A1)
/~XIOW: U3.66 (~IOW), U13.4 (A2)
/~XMEMR: U3.67 (~MEMR), U13.6 (A3)
/~XMEMW: U3.68 (~MEMW), U13.8 (A4)
GND: BUS1.1 (GND), BUS1.10 (GND), BUS1.31 (GND), C1.2, C2.2, C3.2, C4.2, C5.2, C6.2, C7.2, C8.2, C9.2, C10.2, C11.2, C12.2, C13.2, C14.2, C15.2, C16.2, C17.2, C18.2, C19.2, C20.2, C22.2, C23.2, D2.1 (K), HOLE1.1, HOLE2.1, JP2.1, P1.3, P1.~, P3.2, Q1.1 (E), R7.1, SW1.1, SW1.GND, SW2.1, SW2.2, SW2.3, SW3.6, SW3.7, SW3.8, SW3.9, SW3.10, U1.1 (GND), U1.20 (GND), U1.33 (~MX), U2.1 (GND), U2.20 (GND), U3.2 (GND), U3.11 (A64K), U3.22 (GND), U3.32 (PTYIN), U3.42 (GND), U3.64 (GND), U4.16 (GND), U5.16 (GND), U6.16 (GND), U7.1 (~OE), U7.10 (GND), U8.1 (~OE), U8.10 (GND), U9.1 (~OE), U9.2 (D0), U9.3 (D1), U9.4 (D2), U9.5 (D3), U9.10 (GND), U10.10 (GND), U11.10 (GND), U12.1 (~G), U12.10 (GND), U12.11 (A1), U12.13 (A2), U12.19 (~G), U13.1 (~G), U13.10 (GND), U13.19 (~G), U14.7 (GND), U14.9, U14.10, U15.8 (GND), U16.10 (GND)
unnamed: C20.1, R5.1, U3.15 (~REST)
unnamed: C21.1, X1.1
unnamed: C21.2, R8.2, U3.21 (X2)
unnamed: C22.1, R8.1, U3.23 (X1), X1.2
unnamed: C23.1, Q1.3 (C), R1.2
unnamed: D1.1 (K), U15.7 (GP0/CIN+/ISCPDAT)
unnamed: D2.2 (A), R4.2
unnamed: P2.1, R1.1
unnamed: P2.2, SP1.1
unnamed: Q1.2 (B), R6.1
unnamed: R2.2, U12.12 (Y4)
unnamed: R3.2, U12.18 (Y1)
unnamed: RR5.2, SW3.1, U16.18 (I/O2)
unnamed: RR5.3, SW3.2, U16.17 (I/O3)
unnamed: RR5.4, SW3.3, U16.4 (I3)
unnamed: RR5.5, SW3.4, U16.3 (I2)
unnamed: RR5.6, SW3.5, U16.2 (I1)
unnamed: U14.3, U14.4
VCC: BUS1.3 (VCC), BUS1.29 (VCC), C1.1, C2.1, C3.1, C4.1, C5.1, C6.1, C7.1, C8.1, C9.1, C10.1, C11.1, C12.1, C13.1, C14.1, C15.1, C16.1, C17.1, C18.1, C19.1, F1.2, JP1.2, P2.4, R4.1, RR1.1 (COM), RR2.1 (COM), RR3.1 (COM), RR4.1 (COM), RR5.1 (COM), SP1.2, U1.40 (VCC), U2.34 (~BHE~/S7), U2.40 (VCC), U3.1 (VCC), U3.43 (VCC), U4.32 (VCC), U5.32 (VCC), U6.32 (VCC), U7.20 (VCC), U8.20 (VCC), U9.20 (VCC), U10.20 (VCC), U11.20 (VCC), U12.20 (VCC), U13.20 (VCC), U14.14 (VCC), U15.1 (VCC), U16.20 (VCC)

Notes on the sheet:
SW3.1: C0000-C7FFF SW3.2: C8000-CFFFF SW3.3: D0000-D7FFF SW3.4: D8000-DFFFF SW3.5: E0000-EFFFF

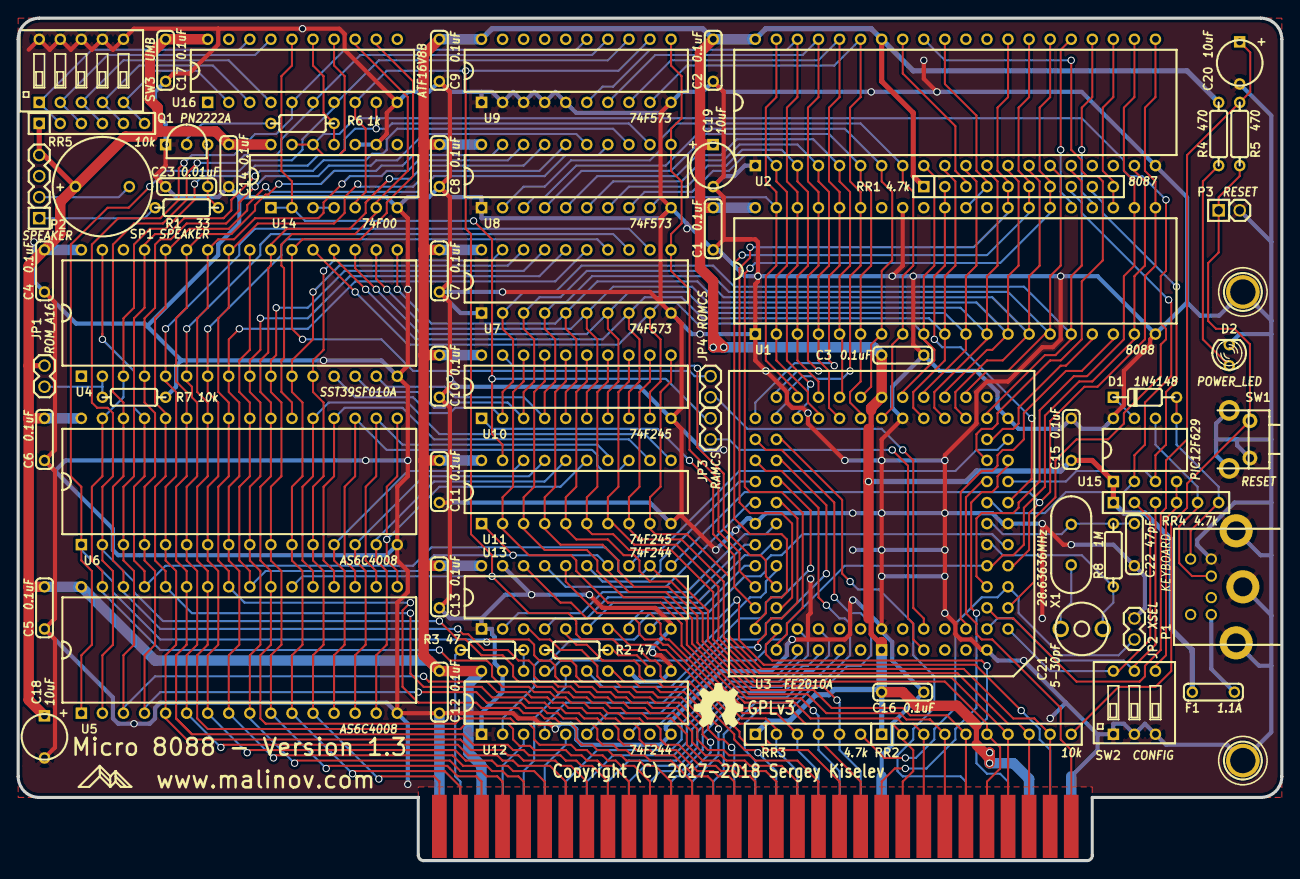
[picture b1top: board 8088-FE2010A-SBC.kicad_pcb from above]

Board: 2 copper layers, 152.4 x 101.6 mm, 71 parts (0 on the bottom side), 149 nets.

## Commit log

2017-09-01 Initial drop - KiCad files for V1.0
2017-09-01 get rid of spaces in filenames
2017-09-01 Add bill of materials
2017-11-01 Add version 1.0 test results and known issues
2017-11-01 Add SPLD files
2017-11-01 Add 1.1 files
2017-11-03 Document the default JP2 position
2017-11-23 SPLD: Renumber switch inputs according to schematic
2017-11-23 images: Add Micro 8088 photo, use it in README
2017-11-25 README: Add a link to Faraday FE2010 datasheet
2017-11-25 Documentation: Add datasheets
2017-11-28 README: Add link to the Mouser BOM
2017-11-28 README: Add description for connectors, jumpers, and switches
2017-11-28 README: Add firmware documentation section
2017-11-28 bios: add 0.9.2 image
2017-11-28 readme: Update BIOS information
2017-11-28 readme: Add OSH Park link, update PCB ordering information
2017-11-28 readme: Describe turbo mode switching
2017-11-28 readme: fix formatting
2017-11-29 bios: add 0.9.3 image
2017-12-01 documentation: Create Faraday FE2010A description document
2017-12-01 Documentation: Update CPU clock information
2017-12-01 README: Remove FE2010/FE2010A documentation, add links to Documentation instead
2017-12-01 README: Misc fixes
2017-12-06 Documentation: Create Building_Instructions.md
2017-12-06 Documentation: Fix URL in Building_Instructions.md
2017-12-06 Documentation: Move Building_Instructions.md to repo root
2017-12-06 Documentation: Spelling fixes
2017-12-06 Documentation: add a link to building instructions
2017-12-06 Documentation: Add F1 polyfuse
2017-12-06 Documentation: remove to do list all items have been completed
2017-12-07 bios: add 0.9.4 image
2018-01-11 FE2010A: Update wait states according to the actual measurements
2018-01-11 FE2010A: Update wait states, take 2
2018-06-12 bios: add 0.9.5 image
2018-06-26 README: Fix AT2XT link, clarify where to get HEX file
2018-09-20 Remove the V20 BIOS issue. It is no longer relevant and might be confusing
2018-09-20 README: Markdown fixes
2018-09-20 Typo fixes
2019-07-02 bios: add 0.9.6 images
2019-11-05 Update 80C88 link to Renesas site
2020-04-01 README: Only one trimmer capacitor is needed
2020-04-02 Building Instructions: There are only 23 capacitors to solder
2021-11-19 README: Update BOM
    Update BOM:
    * Use resistor and resistor arrays that are available in single quantities from Mouser
    * Use Mini DIN PS/2 connector that is available from Mouser
    * Use TDK capacitors for uniformity and a bit of cost savings
    * Update notes on U14 and U16 being mutually exclusive
    * Add a note that the C21 trimmer capacitor can be replaced with a ceramic capacitor
2021-12-06 Fix link to FE2010 datasheet
2021-12-06 README: Mention Proton PT8010AF in the BoM
2021-12-28 README: Update XT2AT VCFED forum link
2022-02-06 Fixed some typos.
2022-04-29 Add BIOS 0.9.8 images
2022-04-29 No need to use micro_8088 branch for BIOS
2023-02-01 Update wait states configuration
2023-02-01 Update the DRAM refresh with new findings
2023-02-01 Add 8088 BIOS version 0.9.9 images
2024-02-13 BIOS - Add links to the 8088 BIOS repo
2024-04-18 Update the link to the AT2XT firmware
2024-04-27 README: Add AT2XT direct download link

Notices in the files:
KiCad/8088-FE2010A-SBC.kicad_pcb:
GPLv3
Copyright (C) 2017-2018 Sergey Kiselev
